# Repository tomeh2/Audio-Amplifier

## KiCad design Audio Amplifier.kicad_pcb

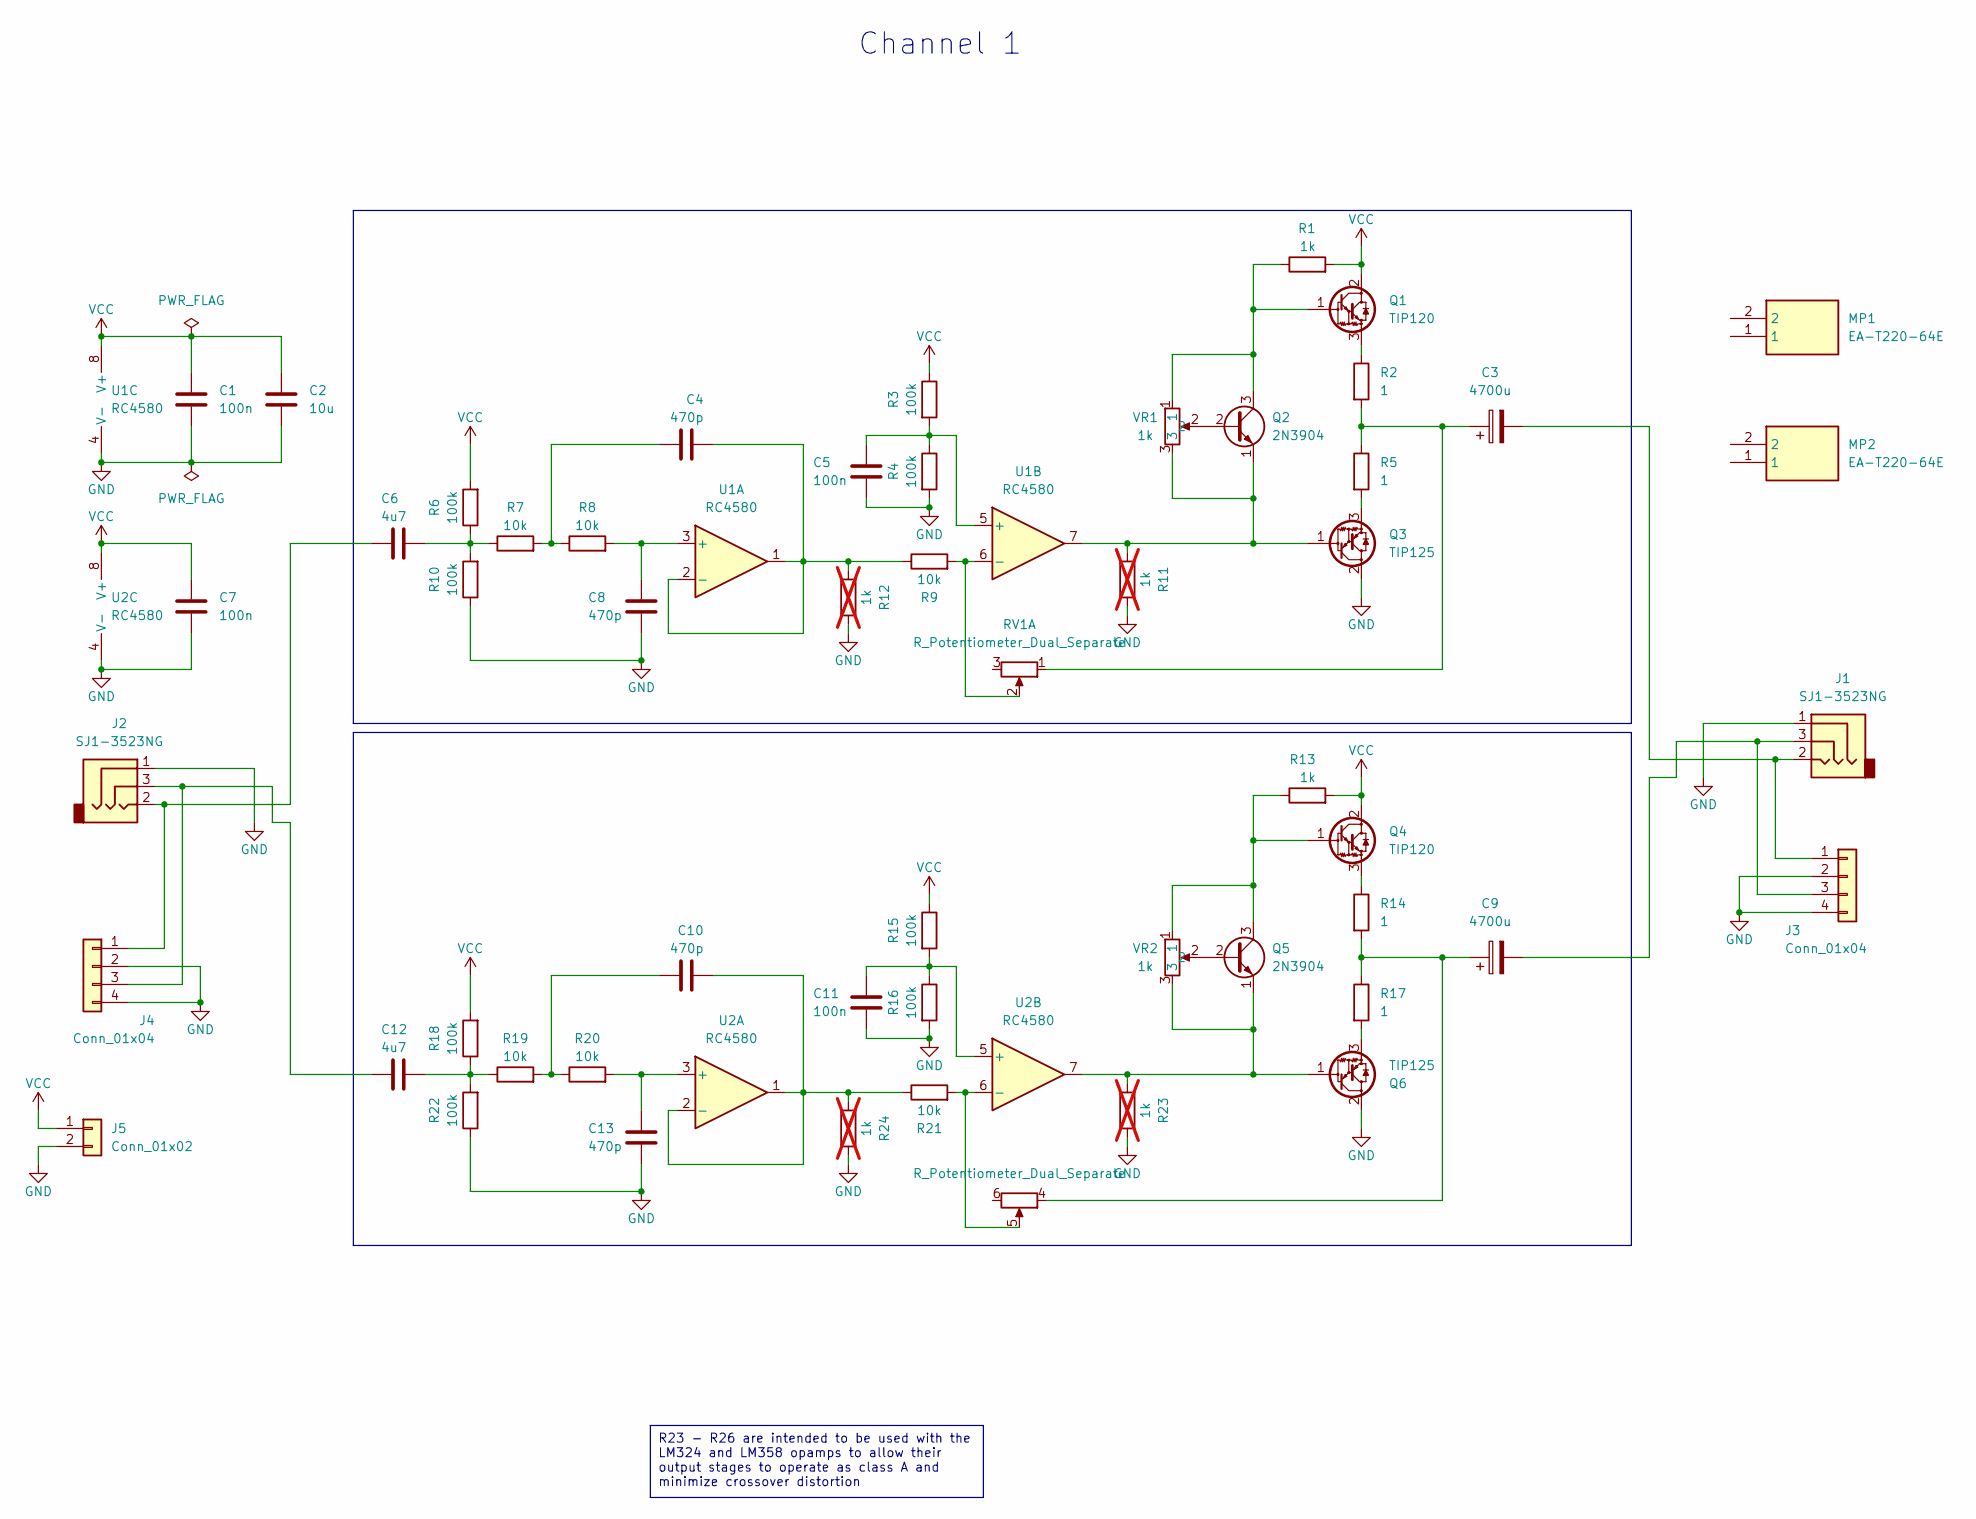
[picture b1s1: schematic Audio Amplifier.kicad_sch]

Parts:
C1, C5, C7, C11: 100n; C_Disc_D4.7mm_W2.5mm_P5.00mm
C2: 10u; CP_Radial_D8.0mm_P3.50mm; Manufacturer_Part_Number UVR2C100MPD; Mouser Part Number 647-UVR2C100MPD
C3, C9: 4700u; CP_Radial_D16.0mm_P7.50mm; Manufacturer_Part_Number UVR1C472MHD; Mouser No. 647-UVY1E472MHD
C4, C8, C10, C13: 470p; C_Disc_D4.7mm_W2.5mm_P5.00mm; Manufacturer_Part_Number K471J15C0GF53L2; Mouser Part Number 594-K471J15C0GF53L2
C6, C12: 4u7; CP_Radial_D5.0mm_P2.00mm; Manufacturer_Part_Number 50MH74R7MEFC5X7; Mouser Part Number 232-50MH74R7MEFC5X7
J1, J2: SJ1-3523NG; SJ13523NG; Mouser Part Number 490-SJ1-3523NG
J3, J4: Conn_01x04; PinHeader_1x04_P2.54mm_Vertical
J5: Conn_01x02; PinHeader_1x02_P2.54mm_Vertical
MP1, MP2: EA-T220-64E; EAT22064E; Mouser Part Number 588-EA-T220-64E
Q1, Q4: TIP120; TO-220-3_Vertical; Manufacturer_Part_Number TIP122; Mouser Part Number 511-TIP122
Q2, Q5: 2N3904; TO-92_Inline; Manufacturer_Part_Number 2N3904; Mouser Part Number 637-2N3904
Q3, Q6: TIP125; TO-220-3_Vertical; Manufacturer_Part_Number TIP127; Mouser Part Number 511-TIP127
R1, R13: 1k; R_Axial_DIN0207_L6.3mm_D2.5mm_P10.16mm_Horizontal; Manufacturer_Part_Number MFR-25FBF52-1K; Mouser Part Number 603-MFR-25FBF52-1K
R2, R5, R14, R17: 1; R_Axial_DIN0411_L9.9mm_D3.6mm_P12.70mm_Horizontal; Manufacturer_Part_Number FMP200JR-52-1R; Mouser No. 594-5073NW1R000J
R3, R4, R6, R10, R15, R16, R18, R22: 100k; R_Axial_DIN0207_L6.3mm_D2.5mm_P10.16mm_Horizontal; Manufacturer_Part_Number MFR-25FBF52-100K; Mouser Part Number 603-MFR-25FBF52-100K
R7, R8, R9, R19, R20, R21: 10k; R_Axial_DIN0207_L6.3mm_D2.5mm_P10.16mm_Horizontal; Manufacturer_Part_Number MFR-25FBF52-10K; Mouser Part Number 603-MFR-25FBF52-10K
R11, R12, R23, R24: 1k; R_Axial_DIN0207_L6.3mm_D2.5mm_P10.16mm_Horizontal; Manufacturer_Part_Number MFR-25FBF52-1K; Mouser Part Number 603-MFR-25FBF52-1K; not fitted
RV1: R_Potentiometer_Dual_Separate; RV122F2015FA10K0072; Manufacturer_Part_Number RV122F-20-15F-A10K-0072; Mouser Part Number 313-1240F-10K
U1, U2: RC4580; DIP-8_W7.62mm; Manufacturer_Part_Number RC4580IP; Mouser No. 595-RC4580IP
VR1, VR2: 1k; 3306P1102; Mouser Part Number 652-3362P-1-102LF

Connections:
GND: C1.2, C2.2, C5.2, C7.2, C8.2, C11.2, C13.2, J1.1, J2.1, J3.2, J3.4, J4.2, J4.4, J5.2, Q3.2 (C), Q6.2 (C), R4.2, R10.1, R11.1, R12.1, R16.2, R22.1, R23.1, R24.1, U1.4 (V-), U2.4 (V-)
unnamed: C3.1, R2.2, R5.1, RV1.1
unnamed: C4.1, R7.2, R8.1
unnamed: C6.1, R6.1, R7.1, R10.2
unnamed: C9.1, R14.2, R17.1, RV1.4
unnamed: C10.1, R19.2, R20.1
unnamed: C12.1, R18.1, R19.1, R22.2
unnamed: C3.2, J1.2, J3.1
unnamed: C9.2, J1.3, J3.3
unnamed: C6.2, J2.2, J4.1
unnamed: C12.2, J2.3, J4.3
unnamed: Q1.1 (B), Q2.3 (C), R1.1, VR1.1
unnamed: Q1.3 (E), R2.1
unnamed: Q2.2 (B), VR1.2
unnamed: Q2.1 (E), Q3.1 (B), R11.2, U1.7, VR1.3
unnamed: Q3.3 (E), R5.2
unnamed: Q4.1 (B), Q5.3 (C), R13.1, VR2.1
unnamed: Q4.3 (E), R14.1
unnamed: Q5.2 (B), VR2.2
unnamed: Q5.1 (E), Q6.1 (B), R23.2, U2.7, VR2.3
unnamed: Q6.3 (E), R17.2
unnamed: C8.1, R8.2, U1.3 (+)
unnamed: C4.2, R9.1, R12.2, U1.1, U1.2 (-)
unnamed: C5.1, R3.2, R4.1, U1.5 (+)
unnamed: R9.2, RV1.2, U1.6 (-)
unnamed: C13.1, R20.2, U2.3 (+)
unnamed: C10.2, R21.1, R24.2, U2.1, U2.2 (-)
unnamed: C11.1, R15.2, R16.1, U2.5 (+)
unnamed: R21.2, RV1.5, U2.6 (-)
VCC: C1.1, C2.1, C7.1, J5.1, Q1.2 (C), Q4.2 (C), R1.2, R3.1, R6.2, R13.2, R15.1, R18.2, U1.8 (V+), U2.8 (V+)

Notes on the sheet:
R23 - R26 are intended to be used with the LM324 and LM358 opamps to allow their output stages to operate as class A and minimize crossover distortion
Channel 1

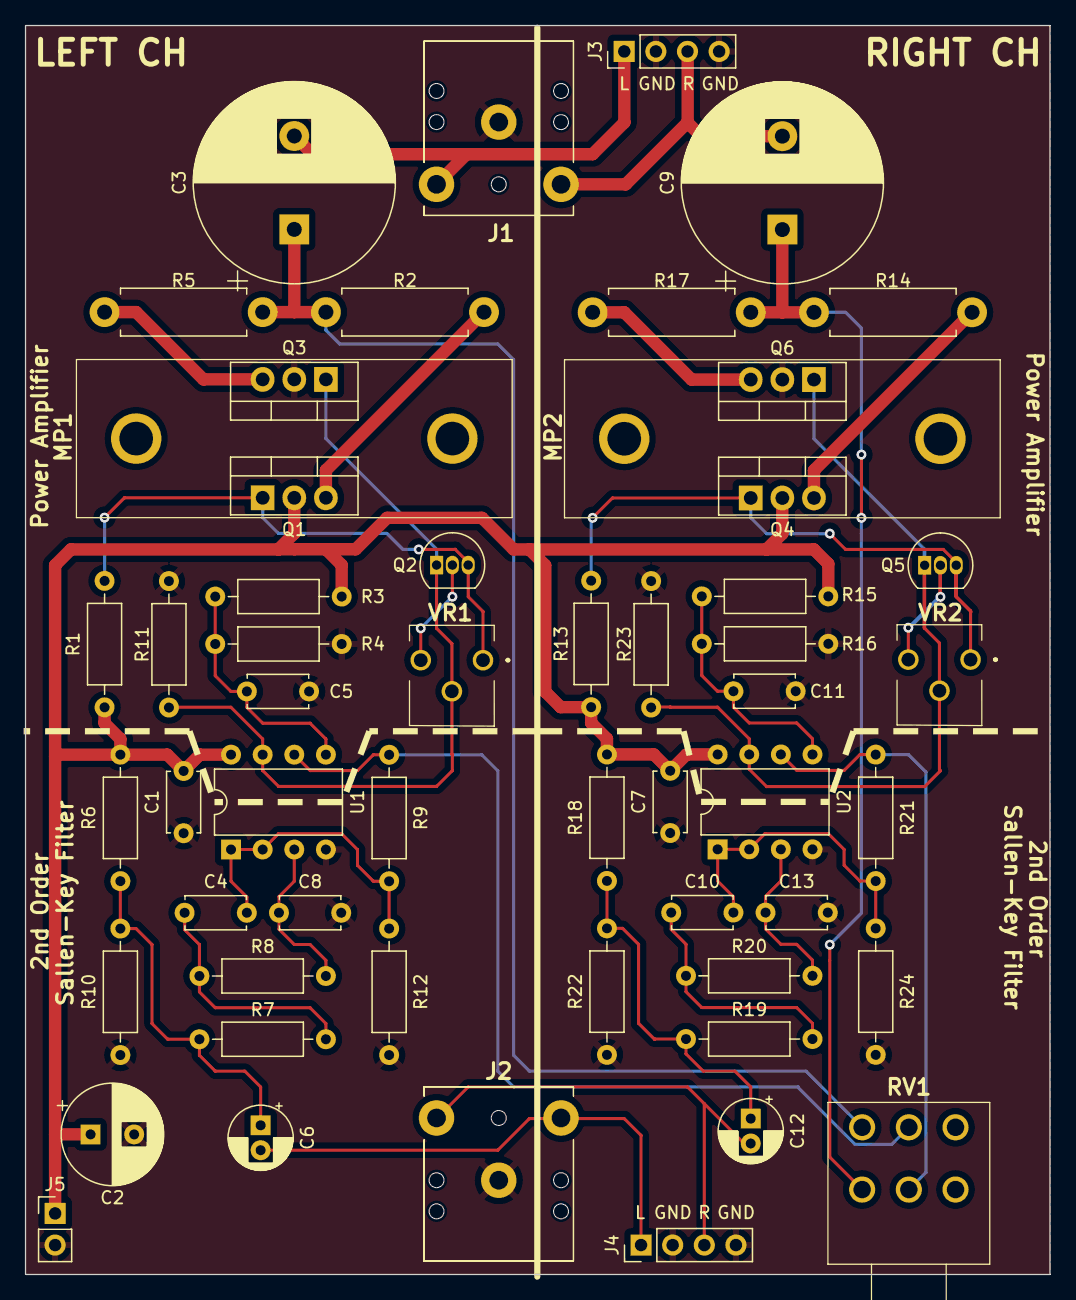
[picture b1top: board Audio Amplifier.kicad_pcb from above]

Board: 2 copper layers, 82.3 x 100.3 mm, 55 parts (0 on the bottom side), 30 nets.

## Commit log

2024-09-01 First commit of a finished project
